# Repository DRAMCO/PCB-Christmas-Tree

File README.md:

# PCB-Christmas-Tree
ChristmasTree contains the Arduino library
DOC contains info about the board.

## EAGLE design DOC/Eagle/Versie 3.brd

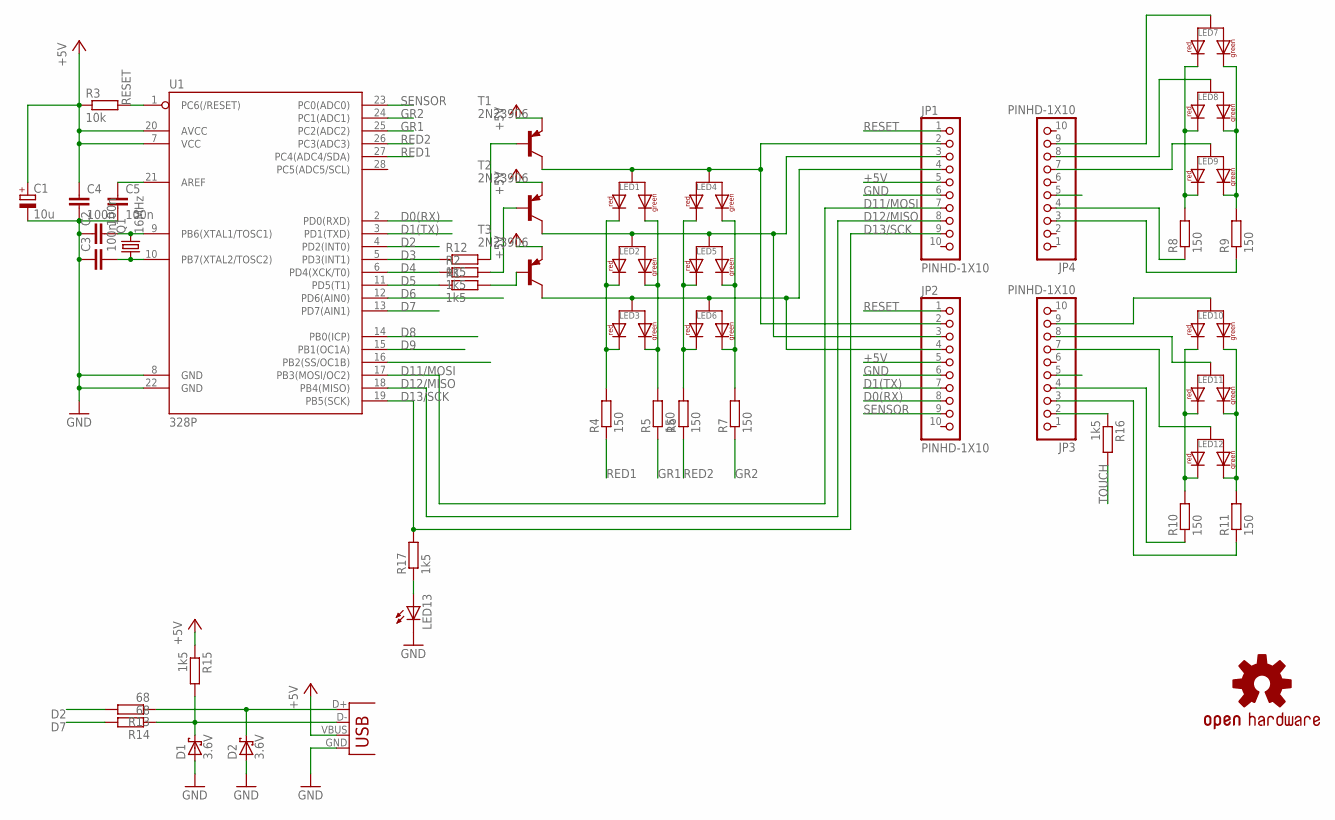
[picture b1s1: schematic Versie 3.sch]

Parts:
C1: 10u; E2-4
C2, C3, C4, C5: 100n; C025-024X044
D1, D2: 3.6V; DO41-7.6
JP1, JP2, JP3, JP4: PINHD-1X10; 1X10-BIG
LED1, LED2, LED3, LED4, LED5, LED6, LED7, LED8, LED9, LED10, LED11, LED12: KPBA-3010SURKCGKC3MM; 3MMLED
LED13: LED5MM
LOGO1: OSHW-LOGOM; OSHW-LOGO-M
Q1: 16MHz; HC49/S
R1, R2, R12, R15, R16, R17: 1k5; 0204/7
R3: 10k; 0204/7
R4, R5, R6, R7, R8, R9, R10, R11: 150; 0204/7
R13, R14: 68; 0204/7
T1, T2, T3: 2N23906; TO92-STRAIGHT
U1: 328P; DIP28
X1: USBMINITHT; USB-MINIB-THT

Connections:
+5V: C1.+, C4.1, JP1.5, JP2.5, R3.1, R15.1, T1.E, T2.E, T3.E, U1.7 (VCC), U1.20 (AVCC), X1.VBUS
D0(RX): JP2.8, U1.2 (PD0(RXD))
D1(TX): JP2.7, U1.3 (PD1(TXD))
D2: R13.2, U1.4 (PD2(INT0))
D3: R12.1, U1.5 (PD3(INT1))
D4: R2.1, U1.6 (PD4(XCK/T0))
D5: R1.1, U1.11 (PD5(T1))
D6: U1.12 (PD6(AIN0))
D7: R14.2, U1.13 (PD7(AIN1))
D8: U1.14 (PB0(ICP))
D9: U1.15 (PB1(OC1A))
D11: U1.16 (PB2(SS/OC1B))
D11/MOSI: JP1.7, U1.17 (PB3(MOSI/OC2))
D12/MISO: JP1.8, U1.18 (PB4(MISO))
D13/SCK: JP1.9, R17.2, U1.19 (PB5(SCK))
GND: C1.-, C2.1, C3.1, C4.2, C5.2, D1.A, D2.A, JP1.6, JP2.6, LED13.K (C), U1.8 (GND), U1.22 (GND), X1.GND
GND2: JP3.5
GND3: JP4.5
GR1: R5.1, U1.25 (PC2(ADC2))
GR2: R7.1, U1.24 (PC1(ADC1))
unnamed: R12.2, T1.B
unnamed: R2.2, T2.B
unnamed: JP3.7, LED12.+
unnamed: R1.2, T3.B
unnamed: D2.C, R13.1, X1.D+
unnamed: D1.C, R14.1, R15.2, X1.D-
unnamed: JP1.2, JP2.2, LED1.+, LED4.+, T1.C
unnamed: LED13.A, R17.1
unnamed: JP1.3, JP2.3, LED2.+, LED5.+, T2.C
unnamed: JP1.4, JP2.4, LED3.+, LED6.+, T3.C
unnamed: LED1.-2, LED2.-2, LED3.-2, R5.2
unnamed: LED4.-2, LED5.-2, LED6.-2, R7.2
unnamed: LED4.-1, LED5.-1, LED6.-1, R6.2
unnamed: LED1.-1, LED2.-1, LED3.-1, R4.2
unnamed: LED7.-1, LED8.-1, LED9.-1, R8.2
unnamed: LED7.-2, LED8.-2, LED9.-2, R9.2
unnamed: LED10.-1, LED11.-1, LED12.-1, R10.2
unnamed: LED10.-2, LED11.-2, LED12.-2, R11.2
unnamed: JP4.7, LED9.+
unnamed: JP3.2, R16.1
unnamed: C2.2, Q1.2, U1.9 (PB6(XTAL1/TOSC1))
unnamed: C3.2, Q1.1, U1.10 (PB7(XTAL2/TOSC2))
unnamed: C5.1, U1.21 (AREF)
unnamed: JP3.4, R10.1
unnamed: JP3.3, R11.1
unnamed: JP3.8, LED11.+
unnamed: JP3.9, LED10.+
unnamed: JP4.4, R8.1
unnamed: JP4.3, R9.1
unnamed: JP4.8, LED8.+
unnamed: JP4.9, LED7.+
RED1: R4.1, U1.27 (PC4(ADC4/SDA))
RED2: R6.1, U1.26 (PC3(ADC3))
RESET: JP1.1, JP2.1, R3.2, U1.1 (PC6(/RESET))
SENSOR: JP2.9, U1.23 (PC0(ADC0))
TOUCH: R16.2

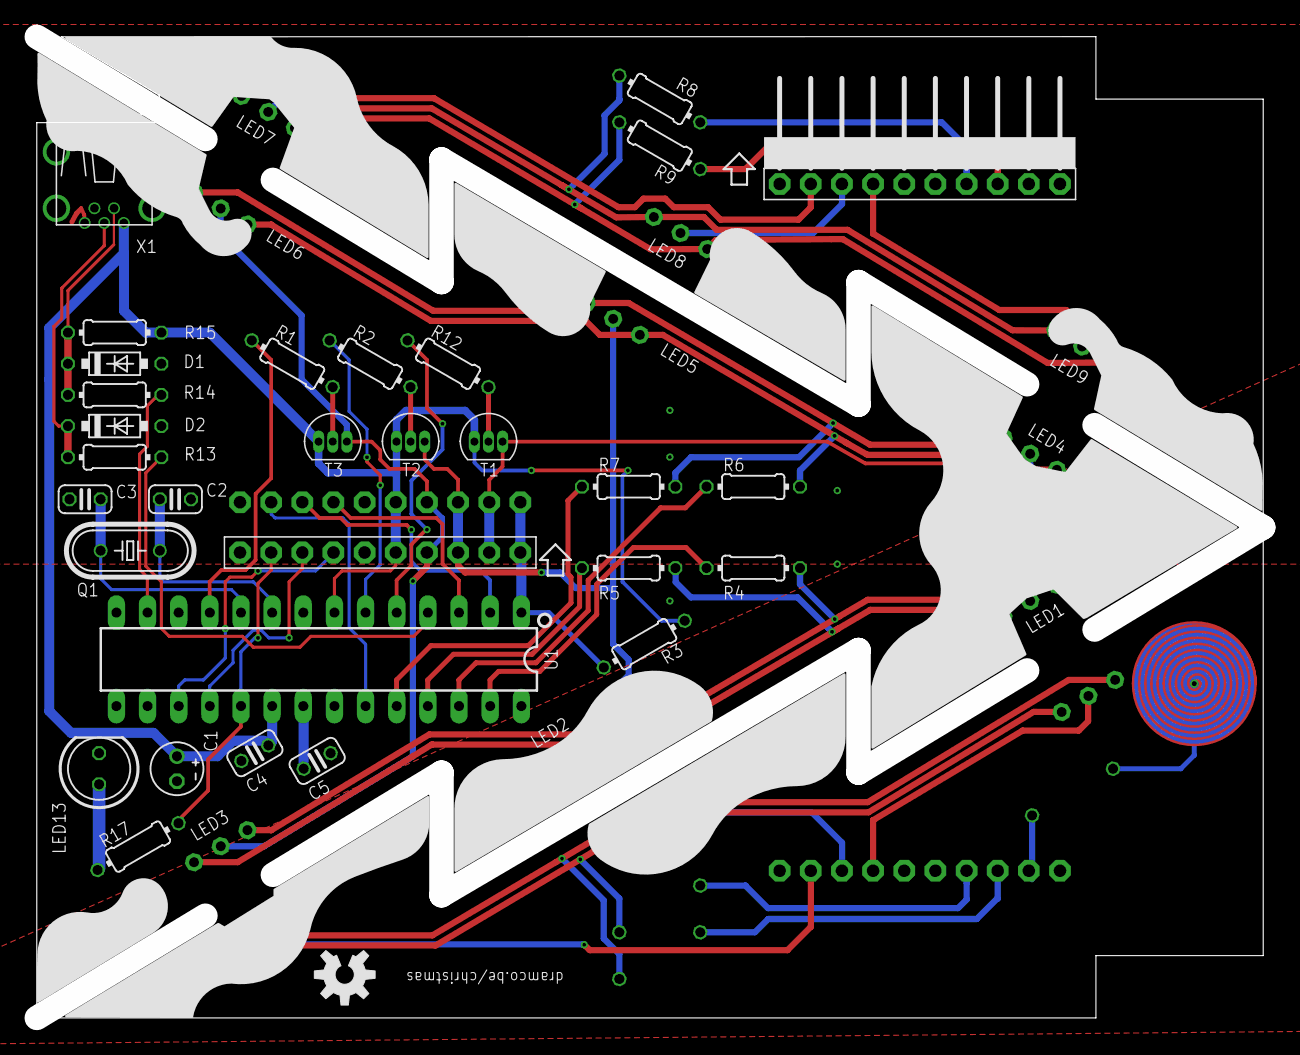
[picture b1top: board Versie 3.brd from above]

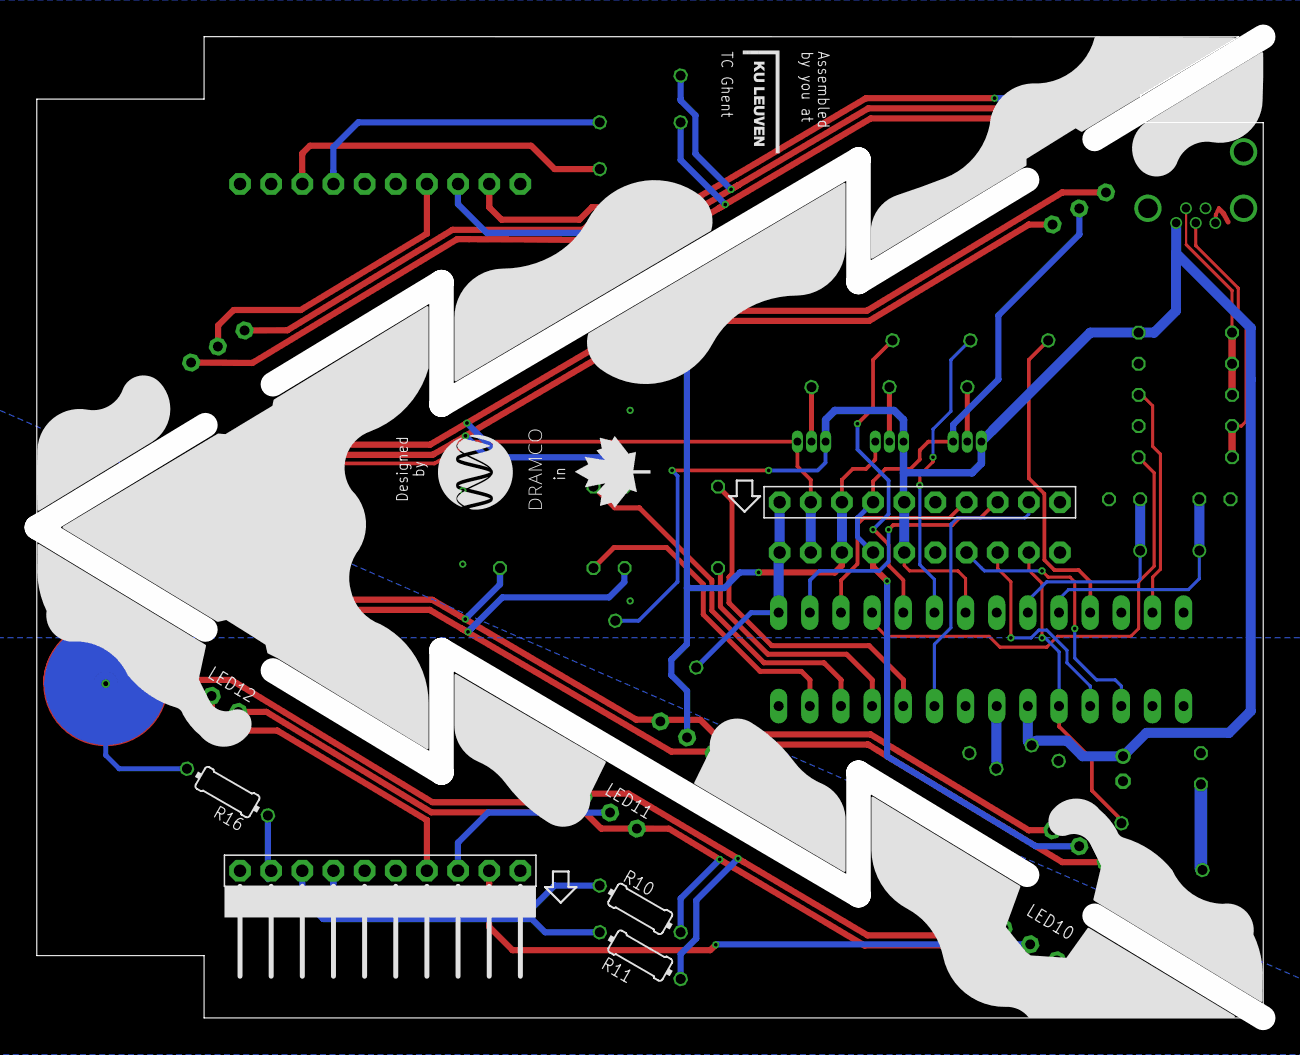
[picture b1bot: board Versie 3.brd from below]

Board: 2 copper layers, 100.0 x 80.0 mm, 48 parts (8 on the bottom side), 49 nets.

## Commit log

2017-11-16 First sketch commit
2017-11-21 Added hardware design
    1) Created DOC folder for documentation.
    2) Added Eagle schematic and board design
2017-11-22 Added Arduino library
2017-11-22 Added extra functionality

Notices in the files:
parts and their libraries:
SparkFun-Aesthetics: Licensing: Creative Commons ShareAlike 4.0 International - https://creativecommons.org/licenses/by-sa/4.0
